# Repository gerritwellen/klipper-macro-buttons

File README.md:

# klipper-macro-buttons

## Hardware
### NanoBreakout:  
Breakout PCB for Arduino Nano to connect 6 Buttons and 6 basic single Color LEDs

### CherryButtons (for Voron)
PCB to mount 3 Cherry MX style switches and 3 LEDs  
Can be used with [meteyou's GCode Buttons](https://github.com/VoronDesign/VoronUsers/tree/master/legacy_printers/printer_mods/meteyou/gcode_buttons) or in combination with the provided [STL](/STLs/Mountx3.stl) and the keycaps by meteyou

## Flashing Arduino Nano
- Generate klipper.bin as outlined in the [klipper documentation](https://www.klipper3d.org/Installation.html#building-and-flashing-the-micro-controller)
- Flash using `avrdude -c arduino -p m328p -P /dev/serial/by-id/<YOUR-ID> -b 57600 -U flash:w:out/klipper.elf.hex:i`

## Klipper Config
Example Config located in [Config Folder](/Config)

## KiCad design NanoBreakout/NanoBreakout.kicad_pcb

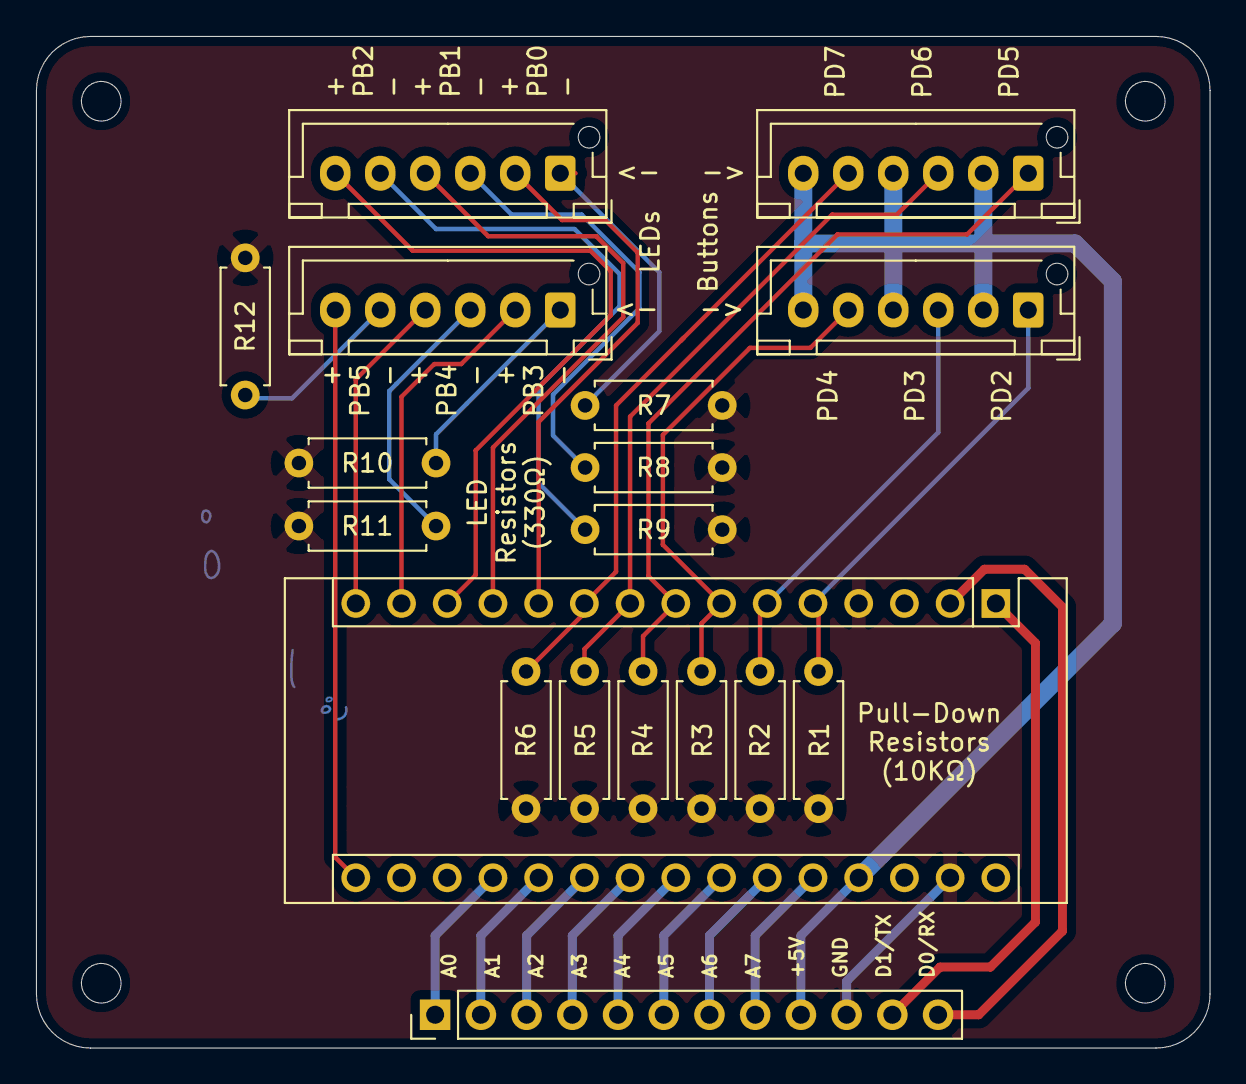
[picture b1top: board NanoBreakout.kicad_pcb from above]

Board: 2 copper layers, 65.2 x 56.2 mm, 23 parts (1 on the bottom side), 30 nets.

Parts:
A1: Arduino_Nano
G2: Graphic; dino1
H1, H2, H3, H4: MountingHole; MountingHole_2.2mm_M2_ISO7380
J1, J2, J3, J4: Conn_01x06; JST_XH_B6B-XH-AM_1x06_P2.50mm_Vertical
J5: Conn_01x12; PinHeader_1x12_P2.54mm_Vertical
R1, R2, R3, R4, R5, R6: 10k; R_Axial_DIN0207_L6.3mm_D2.5mm_P7.62mm_Horizontal
R7, R8, R9, R10, R11, R12: 330; R_Axial_DIN0207_L6.3mm_D2.5mm_P7.62mm_Horizontal

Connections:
+5V: A1.27, J1.2, J1.4, J1.6, J2.2, J2.4, J2.6, J5.9
A0: A1.19, J5.1
A1: A1.20, J5.2
A2: A1.21, J5.3
A3: A1.22, J5.4
A4: A1.23, J5.5
A5: A1.24, J5.6
A6: A1.25, J5.7
A7: A1.26, J5.8
D0: A1.2, J5.12
D1: A1.1, J5.11
D2: A1.5, J1.1, R1.2
D3: A1.6, J1.3, R2.2
D4: A1.7, J1.5, R3.2
D5: A1.8, J2.1, R4.2
D6: A1.9, J2.3, R5.2
D7: A1.10, J2.5, R6.2
D8: A1.11, J3.2
D9: A1.12, J3.4
D10: A1.13, J3.6
D11: A1.14, J4.2
D12: A1.15, J4.4
D13: A1.16, J4.6
GND: A1.4, A1.29, J5.10, R1.1, R2.1, R3.1, R4.1, R5.1, R6.1, R7.1, R8.1, R9.1, R10.1, R11.1, R12.1
unnamed: J3.1, R7.2
unnamed: J3.3, R8.2
unnamed: J3.5, R9.2
unnamed: J4.1, R10.2
unnamed: J4.3, R11.2
unnamed: J4.5, R12.2

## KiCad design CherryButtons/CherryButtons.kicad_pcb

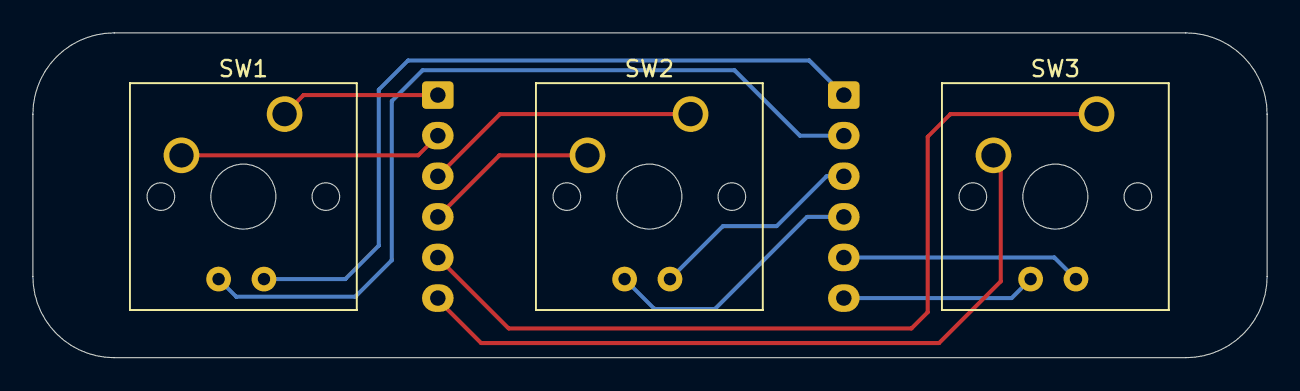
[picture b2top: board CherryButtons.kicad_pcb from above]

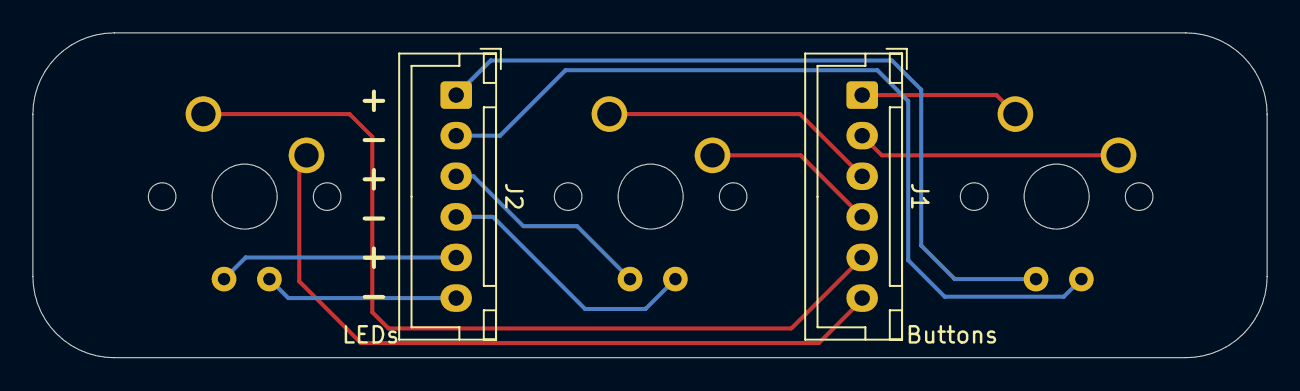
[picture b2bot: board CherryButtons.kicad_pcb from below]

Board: 2 copper layers, 76.0 x 20.0 mm, 5 parts (2 on the bottom side), 12 nets.

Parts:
J1, J2: Conn_01x06; JST_XH_B6B-XH-A_1x06_P2.50mm_Vertical
SW1, SW2, SW3: SW_SPST_LED; SW_Cherry_MX_LED

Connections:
unnamed: J1.1, SW1.1
unnamed: J1.2, SW1.2
unnamed: J1.3, SW2.1
unnamed: J1.4, SW2.2
unnamed: J1.5, SW3.1
unnamed: J1.6, SW3.2
unnamed: J2.1, SW1.4
unnamed: J2.2, SW1.3
unnamed: J2.3, SW2.4
unnamed: J2.4, SW2.3
unnamed: J2.5, SW3.4
unnamed: J2.6, SW3.3

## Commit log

2021-11-11 Added Gerber-files
2021-12-10 Added Example Config, Mount and Documentation
